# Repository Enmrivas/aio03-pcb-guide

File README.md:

# aio03-pcb-guide
 my very first keyboard pcb

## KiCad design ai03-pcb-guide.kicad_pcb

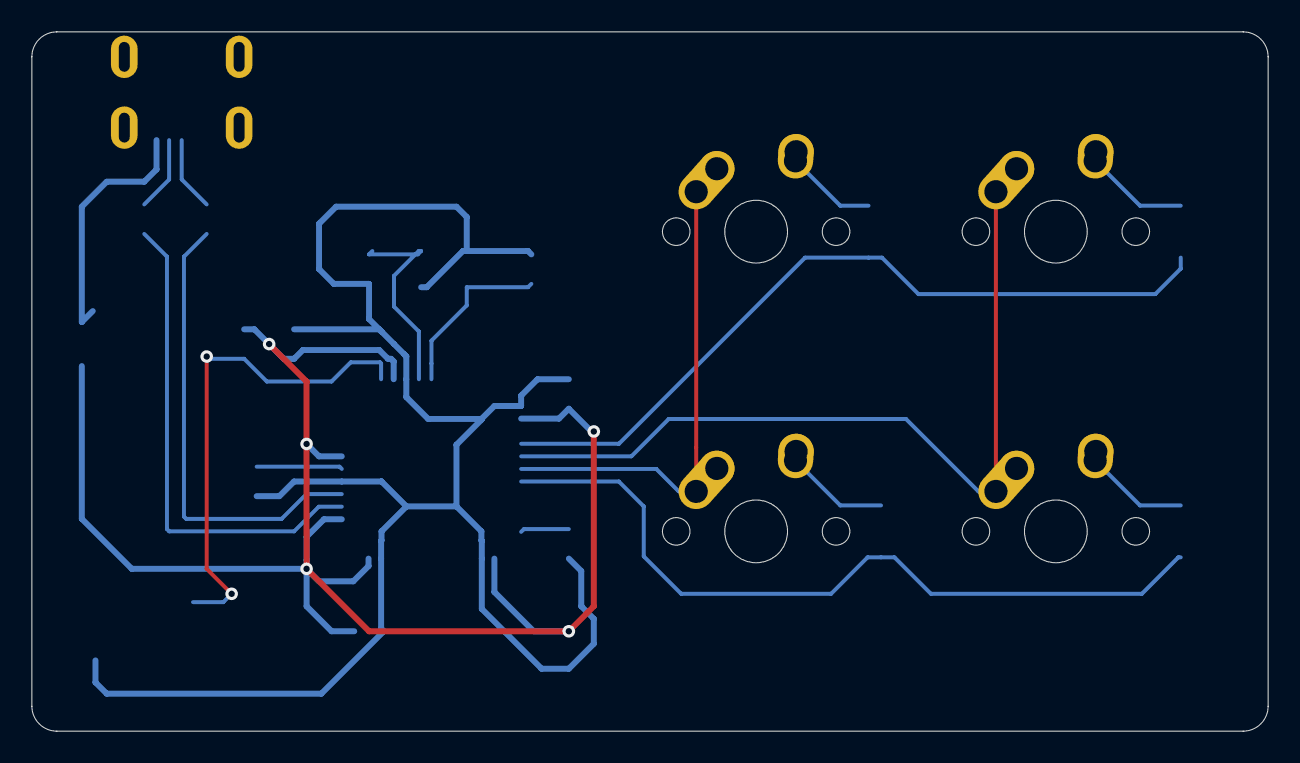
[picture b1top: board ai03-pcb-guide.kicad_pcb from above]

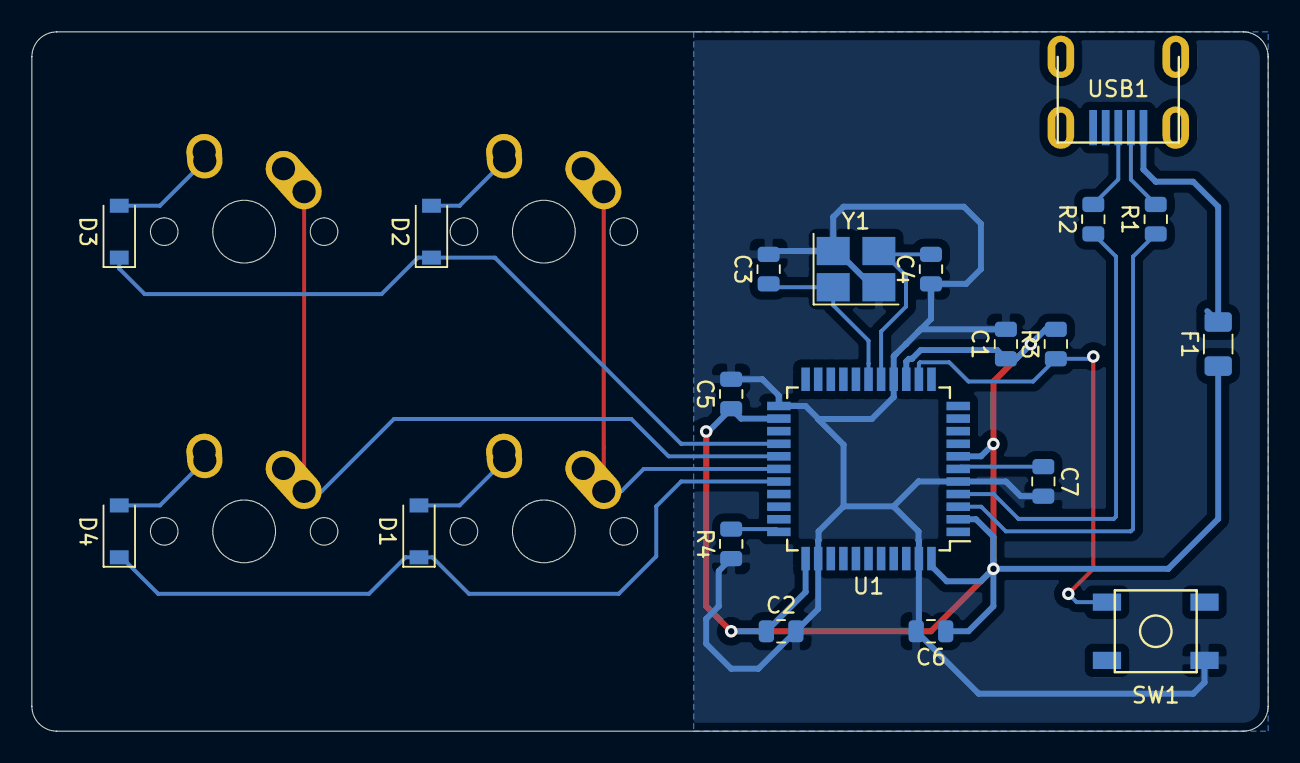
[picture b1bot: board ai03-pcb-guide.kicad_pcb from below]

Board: 2 copper layers, 78.6 x 44.5 mm, 24 parts (20 on the bottom side), 20 nets.

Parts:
C1, C2, C5: 0.1uF; C_0805_2012Metric
C3, C4: 22pF; C_0805_2012Metric
C6: 10uF; C_0805_2012Metric
C7: 1uF; C_0805_2012Metric
D1, D2, D3, D4: SOD-123; D_SOD-123
F1: 500mA; Fuse_1206_3216Metric
MX1, MX2, MX3, MX4: MX-NoLED; MX-1U-NoLED
R1, R2: 22; R_0805_2012Metric
R3, R4: 10k; R_0805_2012Metric
SW1: SW_Push; SKQG-1155865
U1: ATmega32U4-AU; TQFP-44_10x10mm_P0.8mm
USB1: Molex-0548190589
Y1: Crystal_GND24_Small; Crystal_SMD_3225-4Pin_3.2x2.5mm_HandSoldering

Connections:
+5V: C1.1, C2.1, C5.1, C6.1, F1.1, R3.2, U1.2, U1.7, U1.14, U1.24, U1.34, U1.44
COL0: MX1.1, MX2.1, U1.28
COL1: MX3.1, MX4.1, U1.27
D+: R2.2, USB1.3
D-: R1.2, USB1.4
GND: C1.2, C2.2, C3.2, C4.1, C5.2, C6.2, C7.2, R4.1, SW1.1, U1.5, U1.15, U1.23, U1.35, U1.43, Y1.2, Y1.4
unnamed: C3.1, U1.17, Y1.1
unnamed: C4.2, U1.16, Y1.3
unnamed: C7.1, U1.6
unnamed: D1.2, MX2.2
unnamed: D2.2, MX1.2
unnamed: D3.2, MX3.2
unnamed: D4.2, MX4.2
unnamed: R1.1, U1.3
unnamed: R2.1, U1.4
unnamed: R3.1, SW1.2, U1.13
unnamed: R4.2, U1.33
ROW0: D2.1, D3.1, U1.26
ROW1: D1.1, D4.1, U1.29
VCC: F1.2, USB1.5

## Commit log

2022-03-30 kicad project created
2022-03-30 Add submodules
2022-03-30 libraries added.
2022-03-30 Finished schematic.
2022-03-30 components placed
    components placed in their place and routed correctly.
2022-03-30 test complete, gerber file created
2022-03-30 moving gerbers to their folder.
